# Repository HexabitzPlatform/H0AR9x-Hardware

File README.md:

# H0AR91-Hardware
Hexabitz Sensor Hub Module Hardware Design

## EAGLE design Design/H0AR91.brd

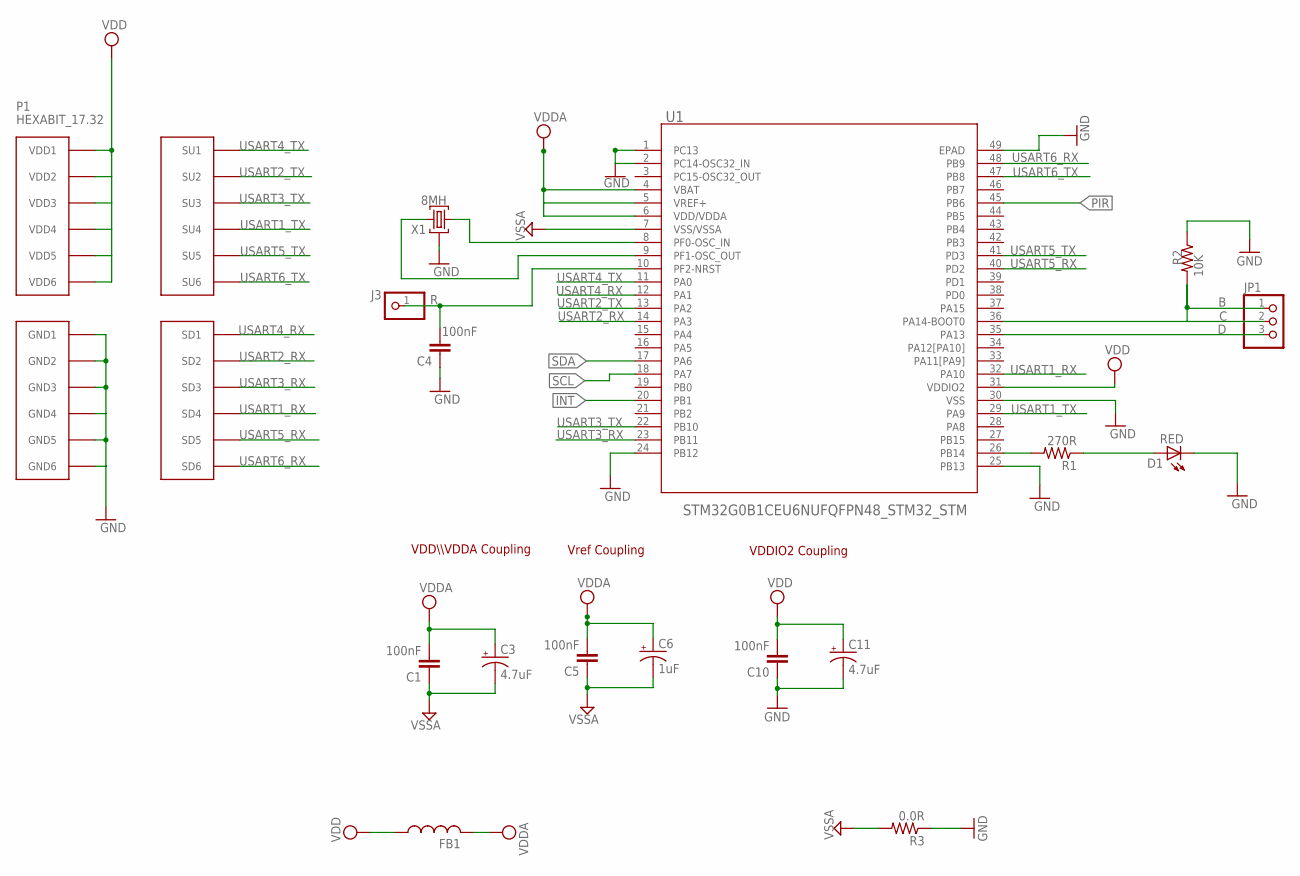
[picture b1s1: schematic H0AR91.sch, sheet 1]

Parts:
C1, C4, C5, C10: 100nF; C-0603; TOLERANCE 10%; VOLTAGE_RATING 16.0 V; MPN '0603YC104K4T2A
C3: 4.7uF; C-0805-POL; TOLERANCE 20%; VOLTAGE_RATING 10.0 V; MPN 10TPU4R7MSI
C6: 1uF; C-0805-POL; TOLERANCE 20%; VOLTAGE_RATING 10.0 V; MPN 'CC0805KKX7R7BB105
C11: 4.7uF; C-0805-POL; TOLERANCE 10%; VOLTAGE_RATING 16.0 V; MPN '10TPU4R7MSI
D1: RED; VLMS1300-GS08
FB1: FB-TDK_MMZ1608Y300B; MPN MMZ1608Y300BTA00
J3: PINHD-1X1; 1X01
JP1: PINHD-1X3; 1X03
P1: HEXABIT_17.32
R1: 270R; R-0603; MPN 'ERJ-3GEYJ271V
R2: 10K; R-0603; MPN '060300J0103T5E
R3: 0.0R; R-0603; MPN RC0603JR-070RL
U1: STM32G0B1CEU6NUFQFPN48_STM32_STM; UFQFPN48_STM32_STM
X1: 8MH; XTALL_CSTCE8M00G52; MPN CSTNE8M00G550000R0

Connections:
C: JP1.1, JP1.2, R2.2, U1.36 (PA14-BOOT0)
D: JP1.3, U1.35 (PA13)
GND: C4.1, C10.1, C11.2 (-), D1.C, P1.PAD_PD7 (GND1), P1.PAD_PD8 (GND2), P1.PAD_PD9 (GND3), P1.PAD_PD10 (GND4), P1.PAD_PD11 (GND5), P1.PAD_PD12 (GND6), R2.1, R3.1, U1.1 (PC13), U1.2 (PC14-OSC32_IN), U1.24 (PB12), U1.25 (PB13), U1.30 (VSS), U1.49 (EPAD), X1.P$2 (2); also elsewhere on the board
GND1: C1.1, C3.2 (-), C5.1, C6.2 (-), R3.2, U1.7 (VSS/VSSA)
INT: U1.20 (PB1); also elsewhere on the board
unnamed: U1.8 (PF0-OSC_IN), X1.P$3 (3)
unnamed: U1.9 (PF1-OSC_OUT), X1.P$1 (1)
unnamed: R1.2, U1.26 (PB14)
unnamed: D1.A, R1.1
PIR: U1.45 (PB6); also elsewhere on the board
R: C4.2, J3.1, U1.10 (PF2-NRST)
SCL: U1.18 (PA7); also elsewhere on the board
SDA: U1.17 (PA6); also elsewhere on the board
USART1_RX: P1.PAD_PD4 (SD4), U1.32 (PA10)
USART1_TX: P1.PAD_PU4 (SU4), U1.29 (PA9)
USART2_RX: P1.PAD_PD2 (SD2), U1.14 (PA3)
USART2_TX: P1.PAD_PU2 (SU2), U1.13 (PA2)
USART3_RX: P1.PAD_PD3 (SD3), U1.23 (PB11)
USART3_TX: P1.PAD_PU3 (SU3), U1.22 (PB10)
USART4_RX: P1.PAD_PD1 (SD1), U1.12 (PA1)
USART4_TX: P1.PAD_PU1 (SU1), U1.11 (PA0)
USART5_RX: P1.PAD_PD5 (SD5), U1.40 (PD2)
USART5_TX: P1.PAD_PU5 (SU5), U1.41 (PD3)
USART6_RX: P1.PAD_PD6 (SD6), U1.48 (PB9)
USART6_TX: P1.PAD_PU6 (SU6), U1.47 (PB8)
VCC: C1.2, C3.1 (+), C5.2, C6.1 (+), FB1.2, U1.4 (VBAT), U1.5 (VREF+), U1.6 (VDD/VDDA)
VDD: C10.2, C11.1 (+), FB1.1, P1.PAD_PU7 (VDD1), P1.PAD_PU8 (VDD2), P1.PAD_PU9 (VDD3), P1.PAD_PU10 (VDD4), P1.PAD_PU11 (VDD5), P1.PAD_PU12 (VDD6), U1.31 (VDDIO2); also elsewhere on the board

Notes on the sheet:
VDDIO2 Coupling
VDD\\\VDDA Coupling
Vref Coupling

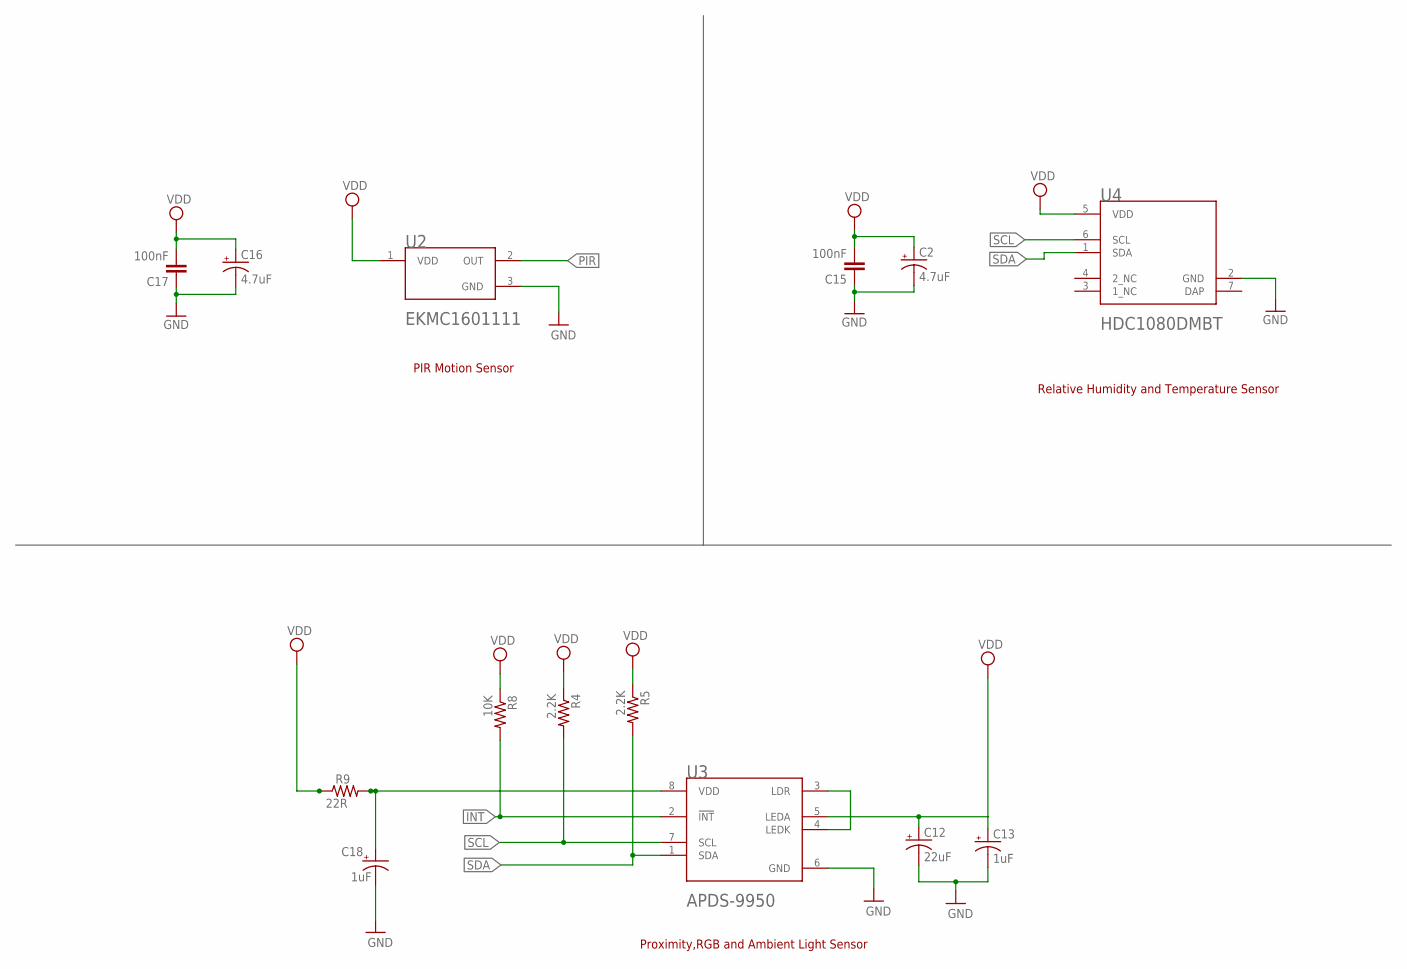
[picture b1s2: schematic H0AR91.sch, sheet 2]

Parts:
C2, C16: 4.7uF; C-0805-POL; TOLERANCE 20%; VOLTAGE_RATING 10.0 V; MPN 10TPU4R7MSI
C12: 22uF; C-0805-POL; TOLERANCE 20%; VOLTAGE_RATING 10.0 V; MPN T491B226K01AT
C13, C18: 1uF; C-0805-POL; TOLERANCE 20%; VOLTAGE_RATING 10.0 V; MPN 'CC0805KKX7R7BB105
C15, C17: 100nF; C-0603; TOLERANCE 10%; VOLTAGE_RATING 16.0 V; MPN '0603YC104K4T2A
R4, R5: 2.2K; R-0603; TOLERANCE 5%; MPN RC0603FR-072K2L
R8: 10K; R-0603; TOLERANCE 5%; MPN '060300J0103T5E
R9: 22R; R1210
U2: PANASONIC_EKMC1601111PANASONIC_EKMC1601111_0_0; PANASONIC_EKMC1601111_0
U3: BROADCOM_APDS-9950BROADCOM_APDS-9950_0_0; BROADCOM_APDS-9960_0
U4: TEXAS_INSTRUMENTS_HDC1080DMBT1TEXAS_INSTRUMENTS_H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; TEXAS_INSTRUMENTS_HDC1080DMBT_1

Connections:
DAP: U4.7 (DAP)
GND: C2.2 (-), C12.2 (-), C13.2 (-), C15.1, C16.2 (-), C17.1, C18.2 (-), U2.3 (GND), U3.6 (GND), U4.2 (GND); also elsewhere on the board
INT: R8.2, U3.2 (!INT!); also elsewhere on the board
unnamed: U3.3 (LDR), U3.4 (LEDK)
unnamed: C18.1 (+), R9.2, U3.8 (VDD)
PIR: U2.2 (OUT); also elsewhere on the board
SCL: R4.2, U3.7 (SCL), U4.6 (SCL); also elsewhere on the board
SDA: R5.2, U3.1 (SDA), U4.1 (SDA); also elsewhere on the board
VDD: C2.1 (+), C12.1 (+), C13.1 (+), C15.2, C16.1 (+), C17.2, R4.1, R5.1, R8.1, R9.1, U2.1 (VDD), U3.5 (LEDA), U4.5 (VDD); also elsewhere on the board

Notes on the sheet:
Proximity,RGB and Ambient Light Sensor
PIR Motion Sensor
Relative Humidity and Temperature Sensor

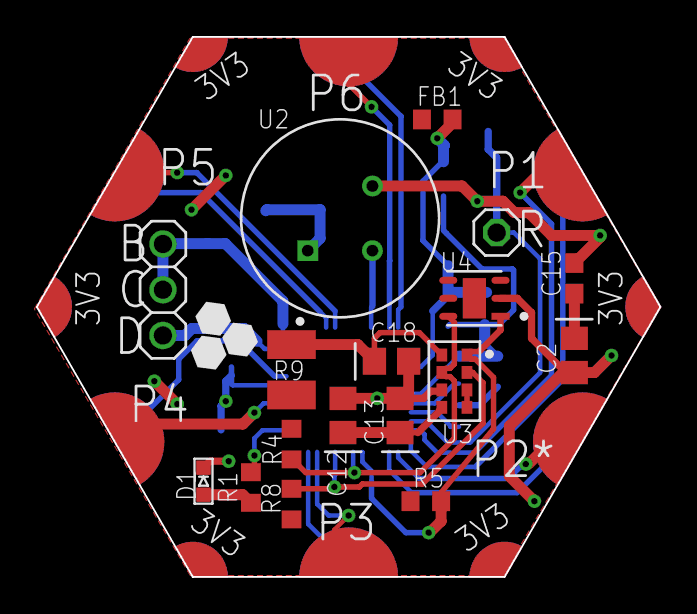
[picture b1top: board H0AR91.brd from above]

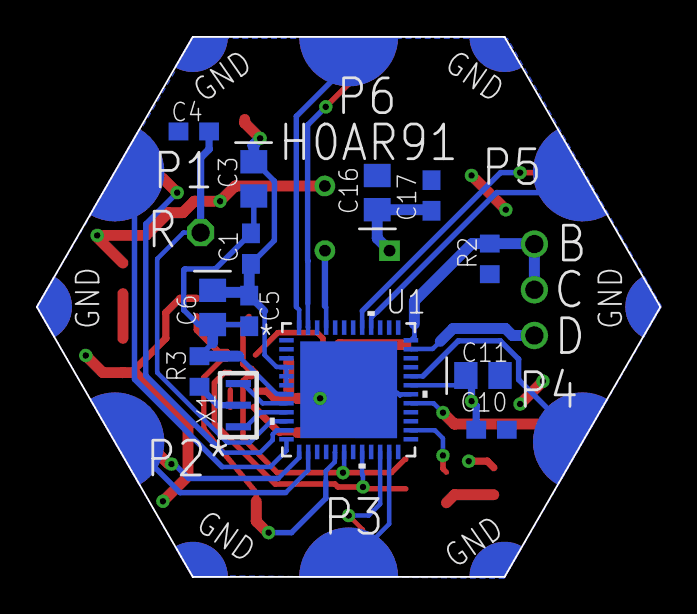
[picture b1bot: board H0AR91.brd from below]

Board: 2 copper layers, 34.6 x 30.0 mm, 31 parts (13 on the bottom side), 29 nets.

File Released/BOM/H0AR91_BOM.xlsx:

Qty | Comment | Designator | Description | MFN | MPN | OCTOPART_URL | Quantity in storage | Position
1 | FB-TDK_MMZ1608Y300BTA00 | FB1 | Ind chip Bead Multi-Layer 30 ohms 25% 100MHZ Ferrite 1,5A 0603Punched paper T/R | TDK | MMZ1608Y300BTA00 | https://octopart.com/mmz1608y300bta00-tdk-7906990?r=sp |  | Frontend
1 | PINHD-1X3 | JP1 | Conn Unshrouded Header HDR 3 POS 2.54mm Solder ST Top Entry Thru-Hole Carton | TE Connectivity | 5-146281-3 | https://octopart.com/5-146281-3-te+connectivity+%2F+amp-3974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 |  | Frontend
1 | PINHD-1X1 | J3 | PCB Header, Unshrouded, Thru 02 Straight Header, .101, AMPMODU Mod II Series | TE Connectivity | 87227-1 | https://octopart.com/87227-1-te+connectivity-39512052?r=sp |  | Frontend
1 | 0.0R | R3 | RES SMD 0.0OHM JUMPER 1/10W 0603 | YAGEO [VR] | RC0603JR-070RL | https://octopart.com/rc0603jr-070rl-yageo-1241539?r=sp |  | Frontend
6 | 100nF | C1,C4,C5,C10,C15,C17 | CAP CER 10% X7R 0603 | AVX CORPORATION | 0603YC104K4T2A | https://octopart.com/0603yc104k4t2a-avx+interconnect+%2F+elc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 |  | Frontend
2 | 10K | R2,R8 | RES 10 K OHM 5% 0603 | Vishay | CRCW060310K0JNEB | https://octopart.com/crcw060310k0jneb-vishay-46603269 |  | Frontend
3 | 1uF | C6,C13,C18 | CAP CER 1UF 16V X7R 0805 | YAGEO [VA] | CC0805KKX7R7BB105 | https://octopart.com/cc0805kkx7r7bb105-yageo-8376555?r=sp |  | Frontend
2 | 2.2K | R4,R5 | RES 2.20K OHM 1/10W 1% 0603 SMD | Yageo | RC0603FR-072K2L | https://octopart.com/rc0603fr-072k2l-yageo-1214512?r=sp |  | Backend
1 | 22R | R9 | Res Thick Film 1210 22 Ohm 5% 1/2W ±200ppm/°C Molded SMD SMD Embossed Carrier T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 | Panasonic | ERJ-T14J220U | https://octopart.com/erj-t14j220u-panasonic-44403795?r=sp | 4900 | Backend
1 | 22uF | C12 | Cap Tant Solid 22uF 10V B CASE 10% (3.5 X 2.8 X 1.9mm) SMD 3528-21 2.3 Ohm 125C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 | Kemet | T491B226K010AT | https://octopart.com/t491b226k016at-kemet-96457?r=sp | 30 | Backend
1 | 270R | R1 | Thick Film Resistors - SMD 0603 270ohms 5% Tol | Panasonic | ERJ-3GEYJ271V | https://octopart.com/erj-3geyj271v-panasonic-55560546?r=sp |  | Frontend
4 | 4.7uF | C2,C3,C11,C16 | CAP TANT 4.7UF 10V 20% 0805 | Panasonic | 10TPU4R7MSI | https://octopart.com/10tpu4r7msi-panasonic-29487748?r=sp | 290 | Frontend/Backend
1 | XTALL_CSTCE8M00G52 | X1 | 8,0000MHZ 33pF SMD MURATA Resonators | Murata | CSTNE8M00G550000R0 | https://octopart.com/cstne8m00g550000r0-murata-91406934?r=sp |  | Frontend
1 | BROADCOM_APDS-9950BROADCOM_APDS-9950_0_0 | U3 | Digital Ambient Light and Proximity Sensor 8-Pin SMD T/R | Broadcom | APDS-9950 | https://octopart.com/apds-9950-avago-39384905 | 12 | Backend
1 | PANASONIC_EKMC1601111PANASONIC_EKMC1601111_0_0 | U2 | Board Mount Motion & Position Sensors Digital 170uA 5m White | Panasonic | EKMC1601111 | https://octopart.com/ekmc1601111-panasonic-18986132?r=sp | 9 | Backend
1 | RED | D1 | Red 0603 130آ° Clear 54 mcd 2 V Surface Mount ChipLED ; | Vishay | VLMS1300-GS08 | https://octopart.com/vlms1300-gs08-vishay-21709201?r=sp&s=0n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 |  | Frontend
1 | STM32G0B1CEU6N | U1 | MCU 32-Bit ARM Cortex-M0+ RISC 512kByte Flash 1.7V to 3.6V 48-Pin UFQFPN Tray | STMicroelectronics | STM32G0B1CEU6N | https://octopart.com/stm32g0b1ceu6n-stmicroelectronics-11636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 |  | Frontend
1 | TEXAS_INSTRUMENTS_HDC1080DMBT1TEXAS_INSTRUMENTS_HDC1080DMBT_0_1 | U4 | HDC1080 Low Power | Texas Instruments | HDC1080DMBT | https://octopart.com/hdc1080dmbt-texas+instruments-68058746?r=sp | 12 | Backend

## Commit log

2022-04-30 -Changing the MC with STM32G0
2022-08-23 Correct Schematic file
2023-02-15 -Correcting some documentaion issues
2024-01-02 -Standarize the files and folders

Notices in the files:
parts and their libraries:
COPYRIGHT: Copyright (C) 2022 Ultra Librarian. All rights reserved.
